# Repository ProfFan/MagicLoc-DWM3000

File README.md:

# MagicLoc DWM3000 module carrier

# LICENSE

CERN OHL-W v2, See `LICENSE`

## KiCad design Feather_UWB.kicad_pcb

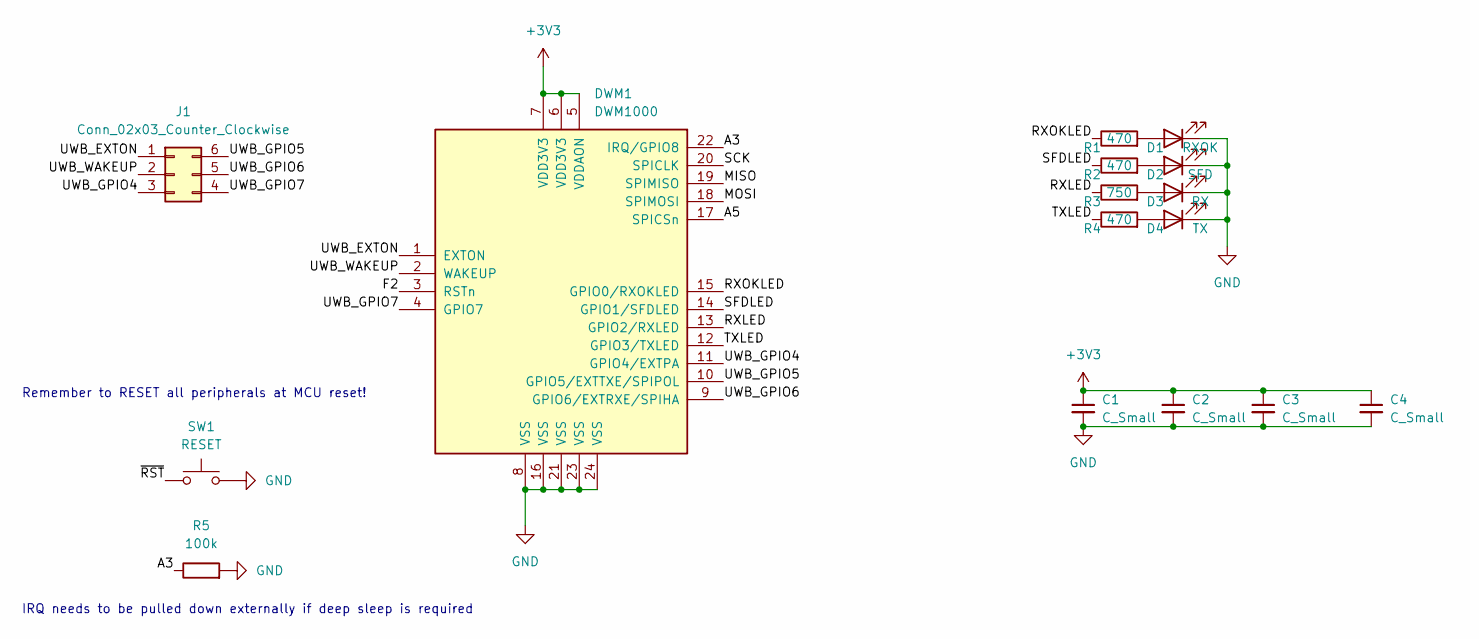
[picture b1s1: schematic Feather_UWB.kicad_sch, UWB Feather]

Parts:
C1, C2, C3: C_Small; C_0805_2012Metric_Pad1.18x1.45mm_HandSolder
C4: C_Small; C_0402_1005Metric
D1: RXOK; LED_0603_1608Metric
D2: SFD; LED_0603_1608Metric
D3: RX; LED_0603_1608Metric
D4: TX; LED_0603_1608Metric
DWM1: DWM1000
J1: Conn_02x03_Counter_Clockwise
R1, R2, R4: 470; R_0603_1608Metric
R3: 750; R_0603_1608Metric
R5: 100k; R_0603_1608Metric
SW1: RESET; SW_SPST_B3U-3000P

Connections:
+3V3: C1.1, C2.1, C3.1, C4.1, DWM1.5 (VDDAON), DWM1.6 (VDD3V3), DWM1.7 (VDD3V3); also elsewhere on the board
/A3: DWM1.22 (IRQ/GPIO8), R5.1; also elsewhere on the board
/A5: DWM1.17 (SPICSn); also elsewhere on the board
/F2: DWM1.3 (RSTn); also elsewhere on the board
/MISO: DWM1.19 (SPIMISO); also elsewhere on the board
/MOSI: DWM1.18 (SPIMOSI); also elsewhere on the board
/RXLED: DWM1.13 (GPIO2/RXLED), R3.1
/RXOKLED: DWM1.15 (GPIO0/RXOKLED), R1.1
/SCK: DWM1.20 (SPICLK); also elsewhere on the board
/SFDLED: DWM1.14 (GPIO1/SFDLED), R2.1
/TXLED: DWM1.12 (GPIO3/TXLED), R4.1
/UWB_EXTON: DWM1.1 (EXTON), J1.1
/UWB_GPIO4: DWM1.11 (GPIO4/EXTPA), J1.3
/UWB_GPIO5: DWM1.10 (GPIO5/EXTTXE/SPIPOL), J1.6
/UWB_GPIO6: DWM1.9 (GPIO6/EXTRXE/SPIHA), J1.5
/UWB_GPIO7: DWM1.4 (GPIO7), J1.4
/UWB_WAKEUP: DWM1.2 (WAKEUP), J1.2
/~RST: SW1.1; also elsewhere on the board
GND: C1.2, C2.2, C3.2, C4.2, D1.1 (K), D2.1 (K), D3.1 (K), D4.1 (K), DWM1.8 (VSS), DWM1.16 (VSS), DWM1.21 (VSS), DWM1.23 (VSS), DWM1.24 (VSS), R5.2, SW1.2; also elsewhere on the board
unnamed: D1.2 (A), R1.2
unnamed: D2.2 (A), R2.2
unnamed: D3.2 (A), R3.2
unnamed: D4.2 (A), R4.2

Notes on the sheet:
IRQ needs to be pulled down externally if deep sleep is required
Remember to RESET all peripherals at MCU reset!

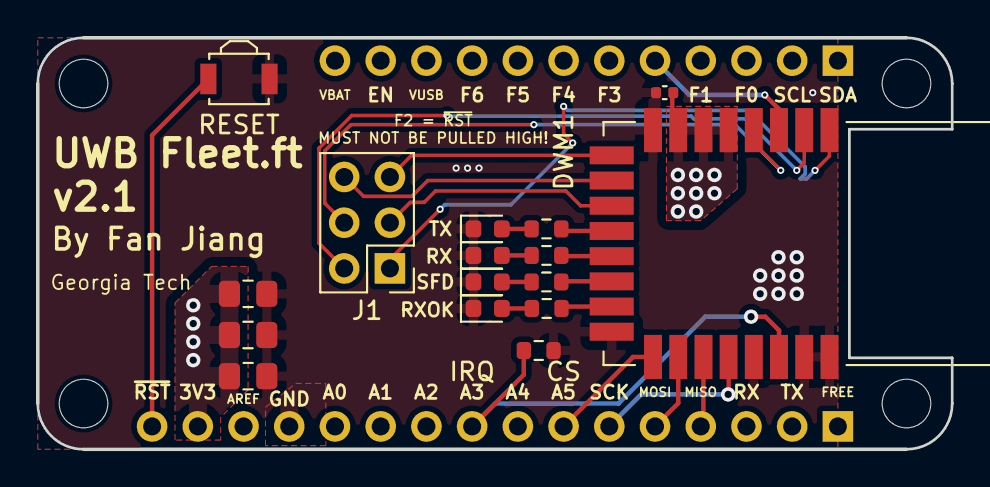
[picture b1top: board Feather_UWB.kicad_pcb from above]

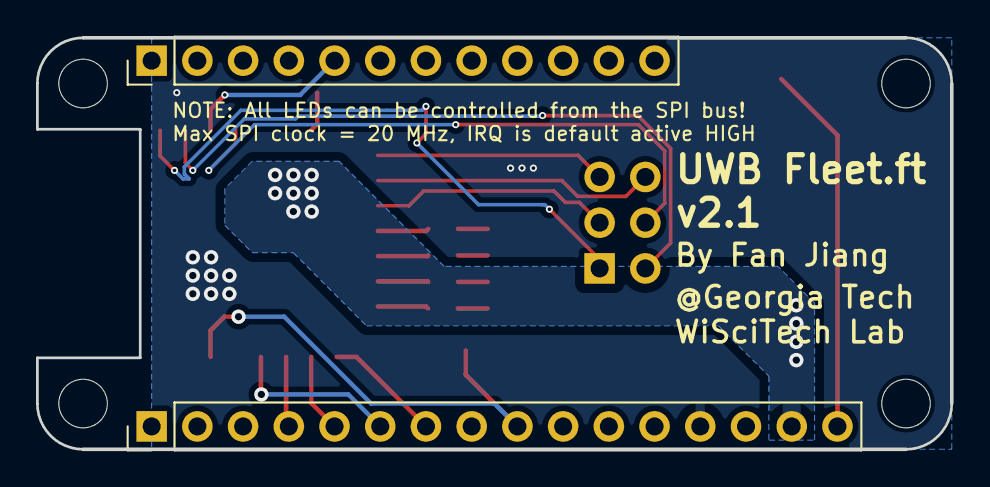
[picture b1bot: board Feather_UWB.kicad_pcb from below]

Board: 2 copper layers, 50.8 x 22.9 mm, 18 parts (2 on the bottom side), 23 nets.

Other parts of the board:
J1#2: feather long; PinHeader_1x16_P2.54mm_Vertical
J2: feather short; PinHeader_1x12_P2.54mm_Vertical

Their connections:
+3V3: J1#2.15; also elsewhere on the board
/A3: J1#2.9; also elsewhere on the board
/A5: J1#2.7; also elsewhere on the board
/F2: J2.5; also elsewhere on the board
/MISO: J1#2.4; also elsewhere on the board
/MOSI: J1#2.5; also elsewhere on the board
/SCK: J1#2.6; also elsewhere on the board
/~RST: J1#2.16; also elsewhere on the board
GND: J1#2.13; also elsewhere on the board

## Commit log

2024-01-23 Before release
